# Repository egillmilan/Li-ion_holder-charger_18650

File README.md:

# Li-ion_holder-charger_18650
A charger/holder for up to four 18650 lithium-ion battery cells. Charging current is a conservative 1A, regardless of how many cells are installed. This is due to the input being USB-C and the need for the device to be able to power whatever the batteries power while charging the batteries. The Ideal diode circuit switches the output to 5V from the USB if the charger is connected, otherwise the output comes from the li-ion cells.

**Some technical notes:**
<ul>
    <li>It is VERY important to only charge the same type of cells in parallel (same capacity and manufactuerer) and the cells need to have the same voltage when connected.</li>
    <li>If a charging timer is to be used, an appropriate capacity for C9 can be found in the datasheet and the RSTRT on jumper should be closed.</li>
    <li>C9 can be omitted if no charging timer is necessary, in that case close the CT off jumper.</li>
    <li>A 0.91" OLED and a dip-package ATmega328P can be added to monitor the voltage of the cells while charging, however this is not necessary for the circuit to function properly. If added, the µC on jumper should be closed.</li>
    <li>If no microcontroller is added, R8 can be ignored as it just acts as a pulldown for the ADC when no battery is connected.
    <li>The LED D1 can also be used to monitor the charging status.</li>
    <li>Watch polarity of cells when installed since there is no protection circuit.</li>
</ul>

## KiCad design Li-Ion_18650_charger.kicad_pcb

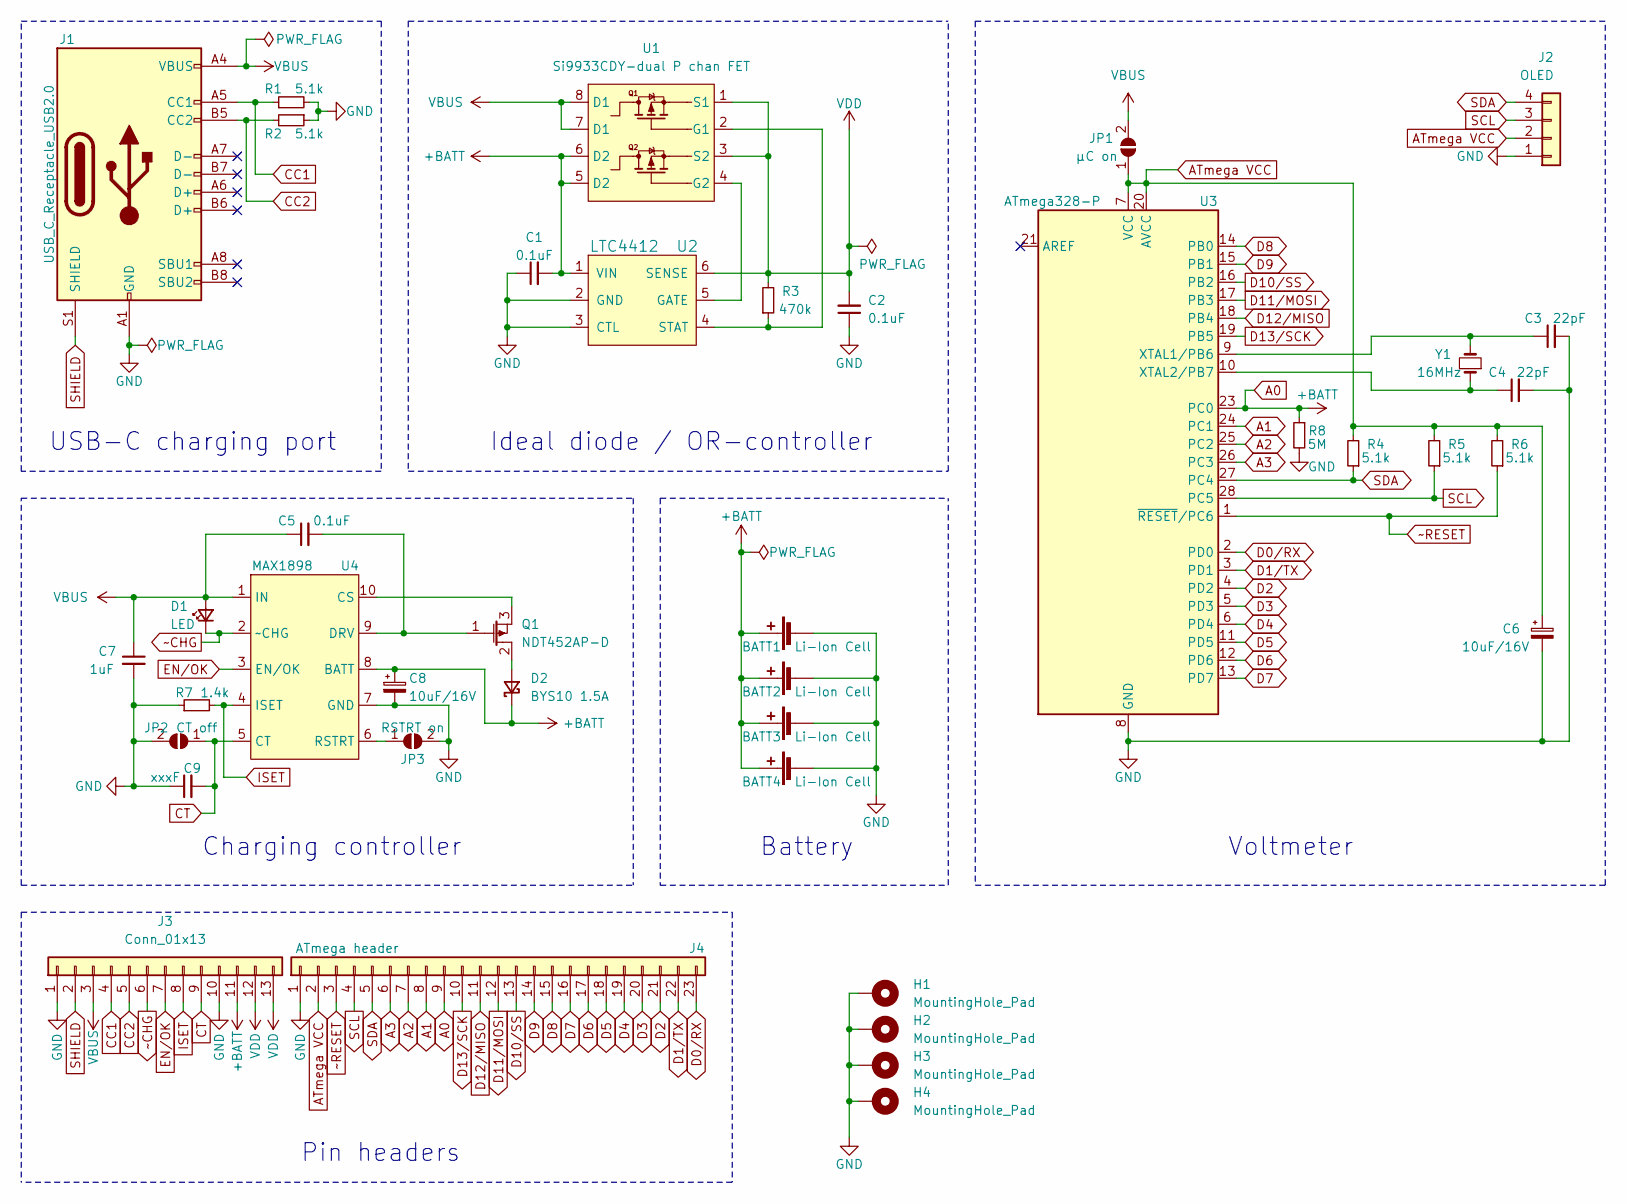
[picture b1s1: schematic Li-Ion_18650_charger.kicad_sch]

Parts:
BATT1, BATT2, BATT3, BATT4: Li-Ion Cell; Keystone_254_holder
C1, C2, C5: 0.1uF; C_1206_3216Metric_Pad1.33x1.80mm_HandSolder
C3, C4: 22pF; C_1206_3216Metric_Pad1.33x1.80mm_HandSolder
C6, C8: 10uF/16V; C_1206_3216Metric_Pad1.33x1.80mm_HandSolder
C7: 1uF; C_1206_3216Metric_Pad1.33x1.80mm_HandSolder
C9: xxxF; C_1206_3216Metric_Pad1.33x1.80mm_HandSolder
D1: LED; LED_1206_3216Metric_Pad1.42x1.75mm_HandSolder
D2: BYS10 1.5A; D_SMA_Handsoldering
H1, H2, H3, H4: MountingHole_Pad; MountingHole_3.2mm_M3_Pad_Via
J1: USB_C_Receptacle_USB2.0; GCT_USB4085-GF-A
J2: OLED; PinSocket_1x04_P2.54mm_Vertical
J3: Conn_01x13; PinHeader_1x13_P2.54mm_Vertical
J4: ATmega header; PinHeader_1x23_P2.54mm_Vertical
JP1: µC on; SolderJumper-2_P1.3mm_Open_Pad1.0x1.5mm
JP2: CT off; SolderJumper-2_P1.3mm_Open_Pad1.0x1.5mm
JP3: RSTRT on; SolderJumper-2_P1.3mm_Open_Pad1.0x1.5mm
Q1: NDT452AP-D; SOT-223-3_TabPin2
R1, R2, R4, R5, R6: 5.1k; R_1206_3216Metric_Pad1.30x1.75mm_HandSolder
R3: 470k; R_1206_3216Metric_Pad1.30x1.75mm_HandSolder
R7: 1.4k; R_1206_3216Metric_Pad1.30x1.75mm_HandSolder
R8: 5M; R_1206_3216Metric_Pad1.30x1.75mm_HandSolder
U1: Si9933CDY-dual P chan FET; SOIC-8_3.9x4.9mm_P1.27mm
U2: LTC4412; TSOT-23-6_HandSoldering; MPN LTC4412ES6#TRMPBF; Digi-Key_PN LTC4412ES6#TRMPBFCT-ND
U3: ATmega328-P; DIP-28_W7.62mm
U4: MAX1898; MSOP-10_3x3mm_P0.5mm
Y1: 16MHz; Crystal_HC49-4H_Vertical

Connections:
A1: J4.8, U3.24 (PC1)
A2: J4.7, U3.25 (PC2)
A3: J4.6, U3.26 (PC3)
ATmega VCC: C6.1, J2.2, J4.2, JP1.1 (A), R4.2, R5.2, R6.2, U3.7 (VCC), U3.20 (AVCC)
CC1: J1.A5 (CC1), J3.4, R1.1
CC2: J1.B5 (CC2), J3.5, R2.2
CT: C9.2, J3.9, JP2.1 (A), U4.5 (CT)
D0/RX: J4.23, U3.2 (PD0)
D1/TX: J4.22, U3.3 (PD1)
D2: J4.21, U3.4 (PD2)
D3: J4.20, U3.5 (PD3)
D4: J4.19, U3.6 (PD4)
D5: J4.18, U3.11 (PD5)
D6: J4.17, U3.12 (PD6)
D7: J4.16, U3.13 (PD7)
D8: J4.15, U3.14 (PB0)
D9: J4.14, U3.15 (PB1)
D10/SS: J4.13, U3.16 (PB2)
D11/MOSI: J4.12, U3.17 (PB3)
D12/MISO: J4.11, U3.18 (PB4)
D13/SCK: J4.10, U3.19 (PB5)
EN/OK: J3.7, U4.3 (EN/OK)
ISET: J3.8, R7.2, U4.4 (ISET)
unnamed: C3.1, U3.9 (XTAL1/PB6), Y1.2
unnamed: C4.1, U3.10 (XTAL2/PB7), Y1.1
unnamed: C5.2, Q1.1, U4.9 (DRV)
unnamed: D2.2 (A), Q1.2
unnamed: JP3.1 (A), U4.6 (RSTRT)
unnamed: Q1.3, U4.10 (CS)
unnamed: R3.1, U1.2 (G1), U2.4 (STAT)
unnamed: U1.4 (G2), U2.5 (GATE)
SCL: J2.3, J4.4, R5.1, U3.28 (PC5)
SDA: J2.4, J4.5, R4.1, U3.27 (PC4)
SHIELD: J1.S1 (SHIELD), J3.2
VBUS: C5.1, C7.1, D1.2 (A), J1.A4 (VBUS), J1.A9 (VBUS), J1.B4 (VBUS), J1.B9 (VBUS), J3.3, JP1.2 (B), U1.7 (D1), U1.8 (D1), U4.1 (IN)
VDD: C2.2, J3.12, J3.13, R3.2, U1.1 (S1), U1.3 (S2), U2.6 (SENSE)
~CHG: D1.1 (K), J3.6, U4.2 (~CHG)
~RESET: J4.3, R6.1, U3.1 (~RESET/PC6)

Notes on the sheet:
USB-C charging port
Charging controller
Pin headers
Ideal diode / OR-controller
Battery
Voltmeter

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
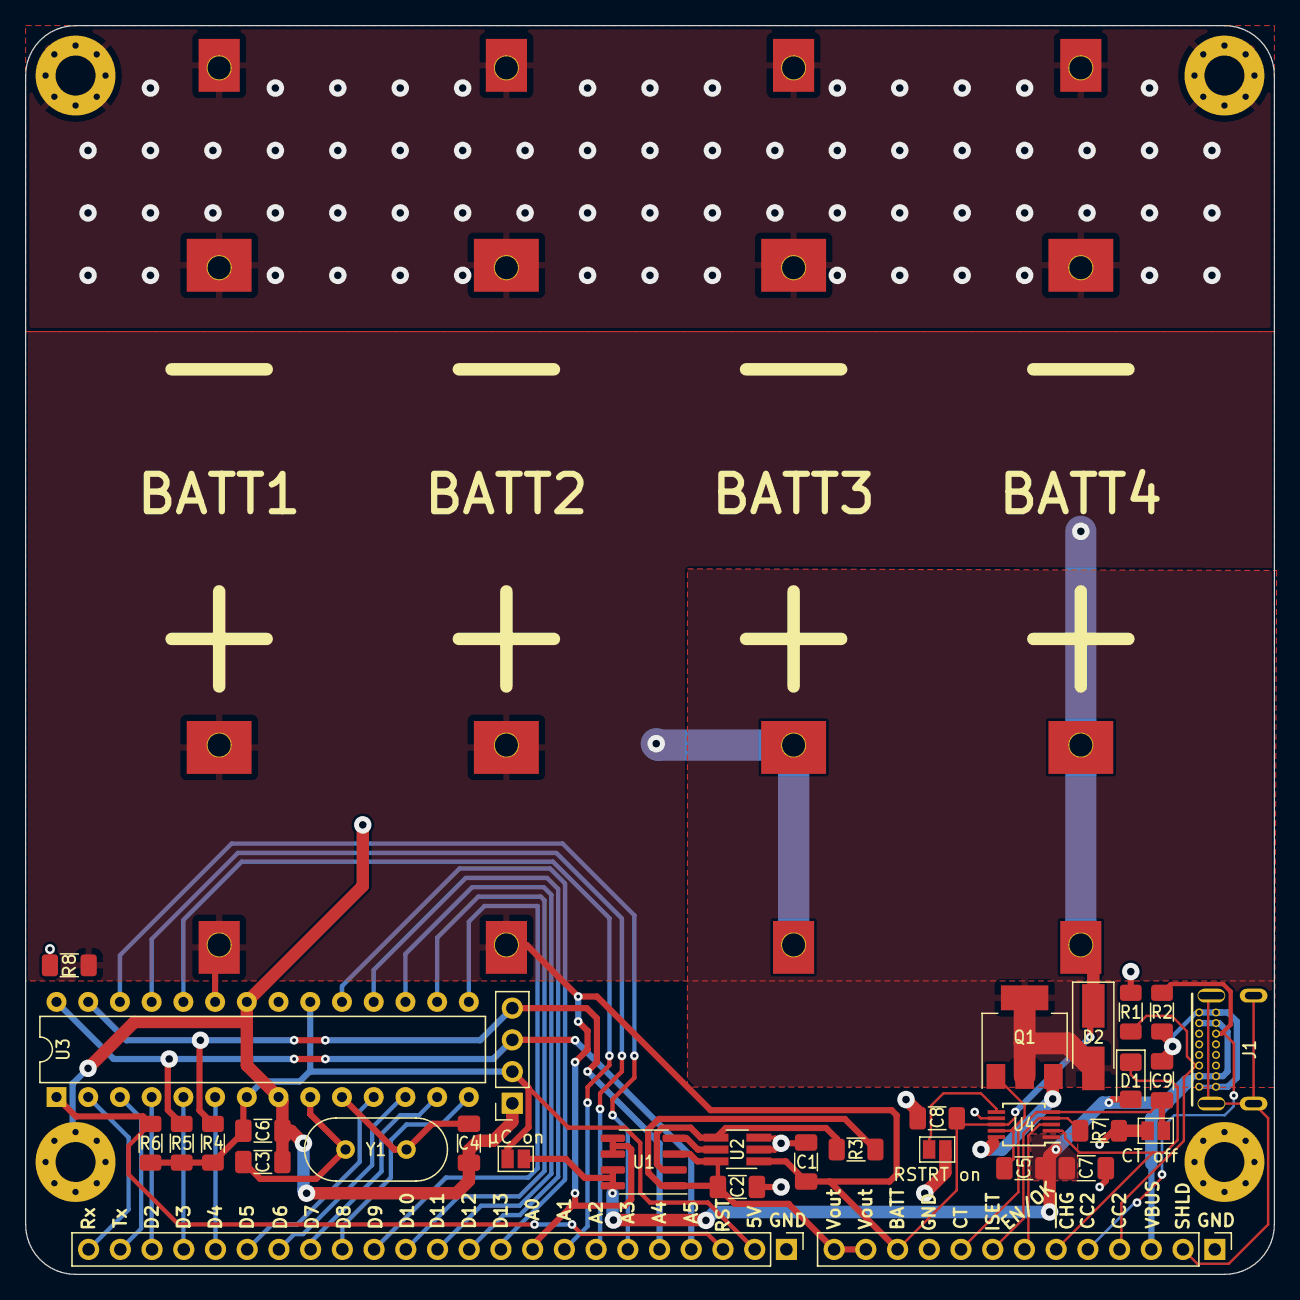
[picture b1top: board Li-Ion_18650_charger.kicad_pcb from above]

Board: 2 copper layers, 100.0 x 100.0 mm, 40 parts (0 on the bottom side), 40 nets.

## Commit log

2021-12-09 Added schematic, pcb and libraries
2021-12-09 not used
